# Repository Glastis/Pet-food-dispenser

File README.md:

# Pet-food-dispenser

One of my cat can eat until he dies (see illustration bellow). I had to prevent this.

I will share the plans once they're done. Ofc it's a wip project, then it could change over time.

## Hardware

### Libraries used

#### Eagle libraries
- [A4988](https://github.com/suzakulab/Eagle-Library-Pololu)
- [ESP12](https://github.com/handiko/ESP-12EF-Eagle-Library)

### Parts

- Stepper: `Nema 17`
- Stepper controller: `A4988`
- Card: `ESP-12E` (but should work with any `ESP8266`)
- Power supply: an old computer PSU. You probably have one or two in your garage, right next to your 512MB RAM parts.

### Schematic 

### Board

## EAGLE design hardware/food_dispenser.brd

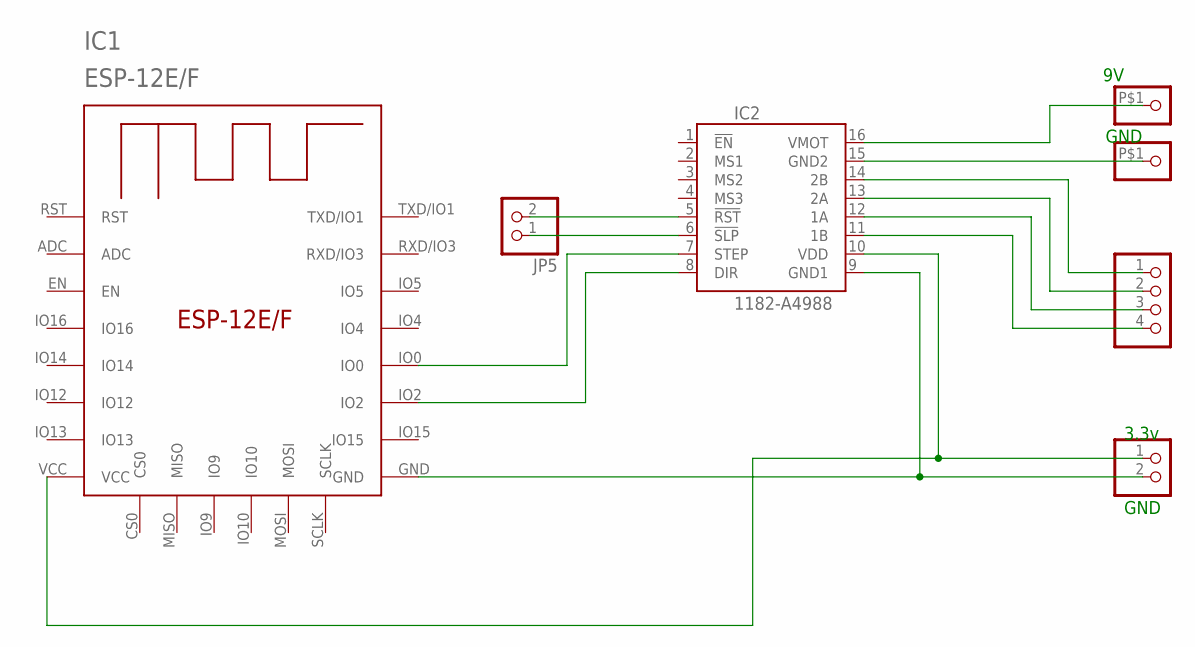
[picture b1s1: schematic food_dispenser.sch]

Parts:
IC1: ESP-12E/F; ESP-12E
IC2: 1182-A4988; A4988
JP1, JP2: PINHD-1X1-BIGPOGO; 1X1-BIGPOGO
JP3, JP5: PINHD-1X2; 1X02
JP4: PINHD-1X4; 1X04

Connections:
GND: IC1.GND, IC2.9 (GND1), JP3.2
unnamed: IC2.15 (GND2), JP2.P$1
unnamed: IC2.16 (VMOT), JP1.P$1
unnamed: IC2.6 (!SLP), JP5.1
unnamed: IC1.VCC, IC2.10 (VDD), JP3.1
unnamed: IC2.14 (2B), JP4.1
unnamed: IC2.13 (2A), JP4.2
unnamed: IC2.12 (1A), JP4.3
unnamed: IC2.11 (1B), JP4.4
unnamed: IC1.IO0, IC2.7 (STEP)
unnamed: IC1.IO2, IC2.8 (DIR)
unnamed: IC2.5 (!RST), JP5.2

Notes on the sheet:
GND
3.3v

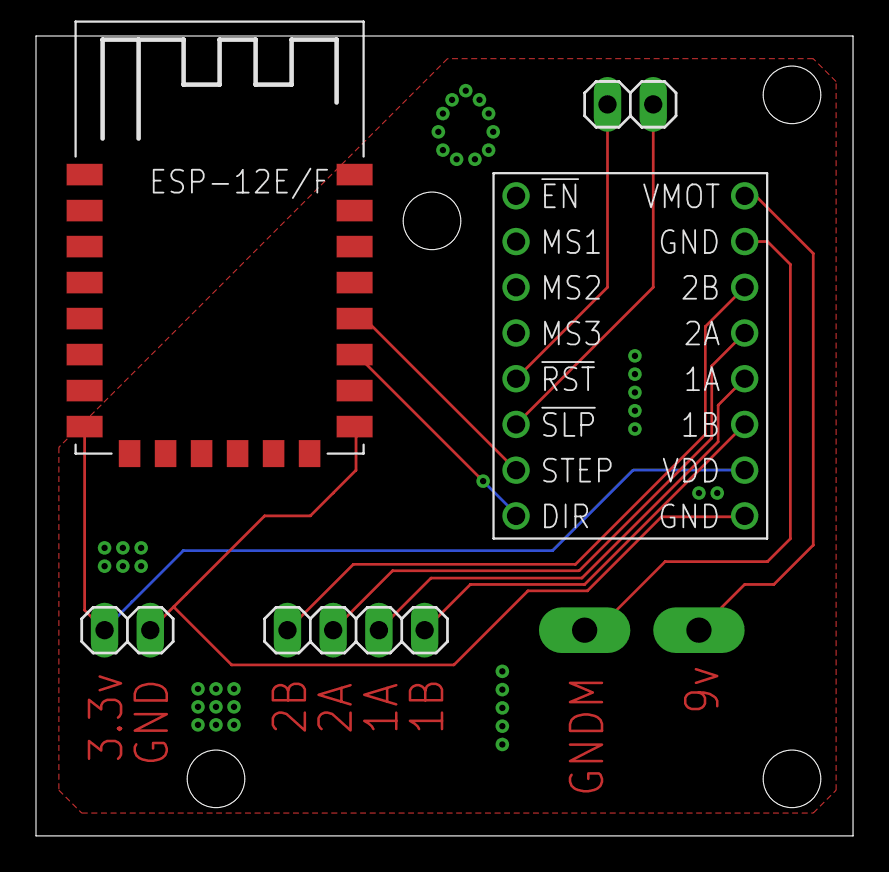
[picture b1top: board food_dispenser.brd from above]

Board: 2 copper layers, 45.4 x 44.4 mm, 7 parts (0 on the bottom side), 12 nets.

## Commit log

2022-10-03 docs: added basic stuff and screen of the schematic to the readme
2022-10-03 docs: fix line wraping in readme
2022-10-03 docs: added board screen to readme
2022-10-03 feat: add schematic
2022-10-03 feat: add board
2022-10-03 docs: add eagle libraries and esp to readme
2022-10-05 feat: add gnd plate, pin names and logo to board
2022-10-05 feat: add top gnd plate, via and fixation holes
2022-10-05 docs: updated board screens
2022-10-06 feat: added endless screw of the device
2022-10-06 docs: spelling in readme
